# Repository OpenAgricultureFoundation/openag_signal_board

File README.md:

# openag_signal_board
Shield for Arduino Mega to easily connect sensors and other communication devices.

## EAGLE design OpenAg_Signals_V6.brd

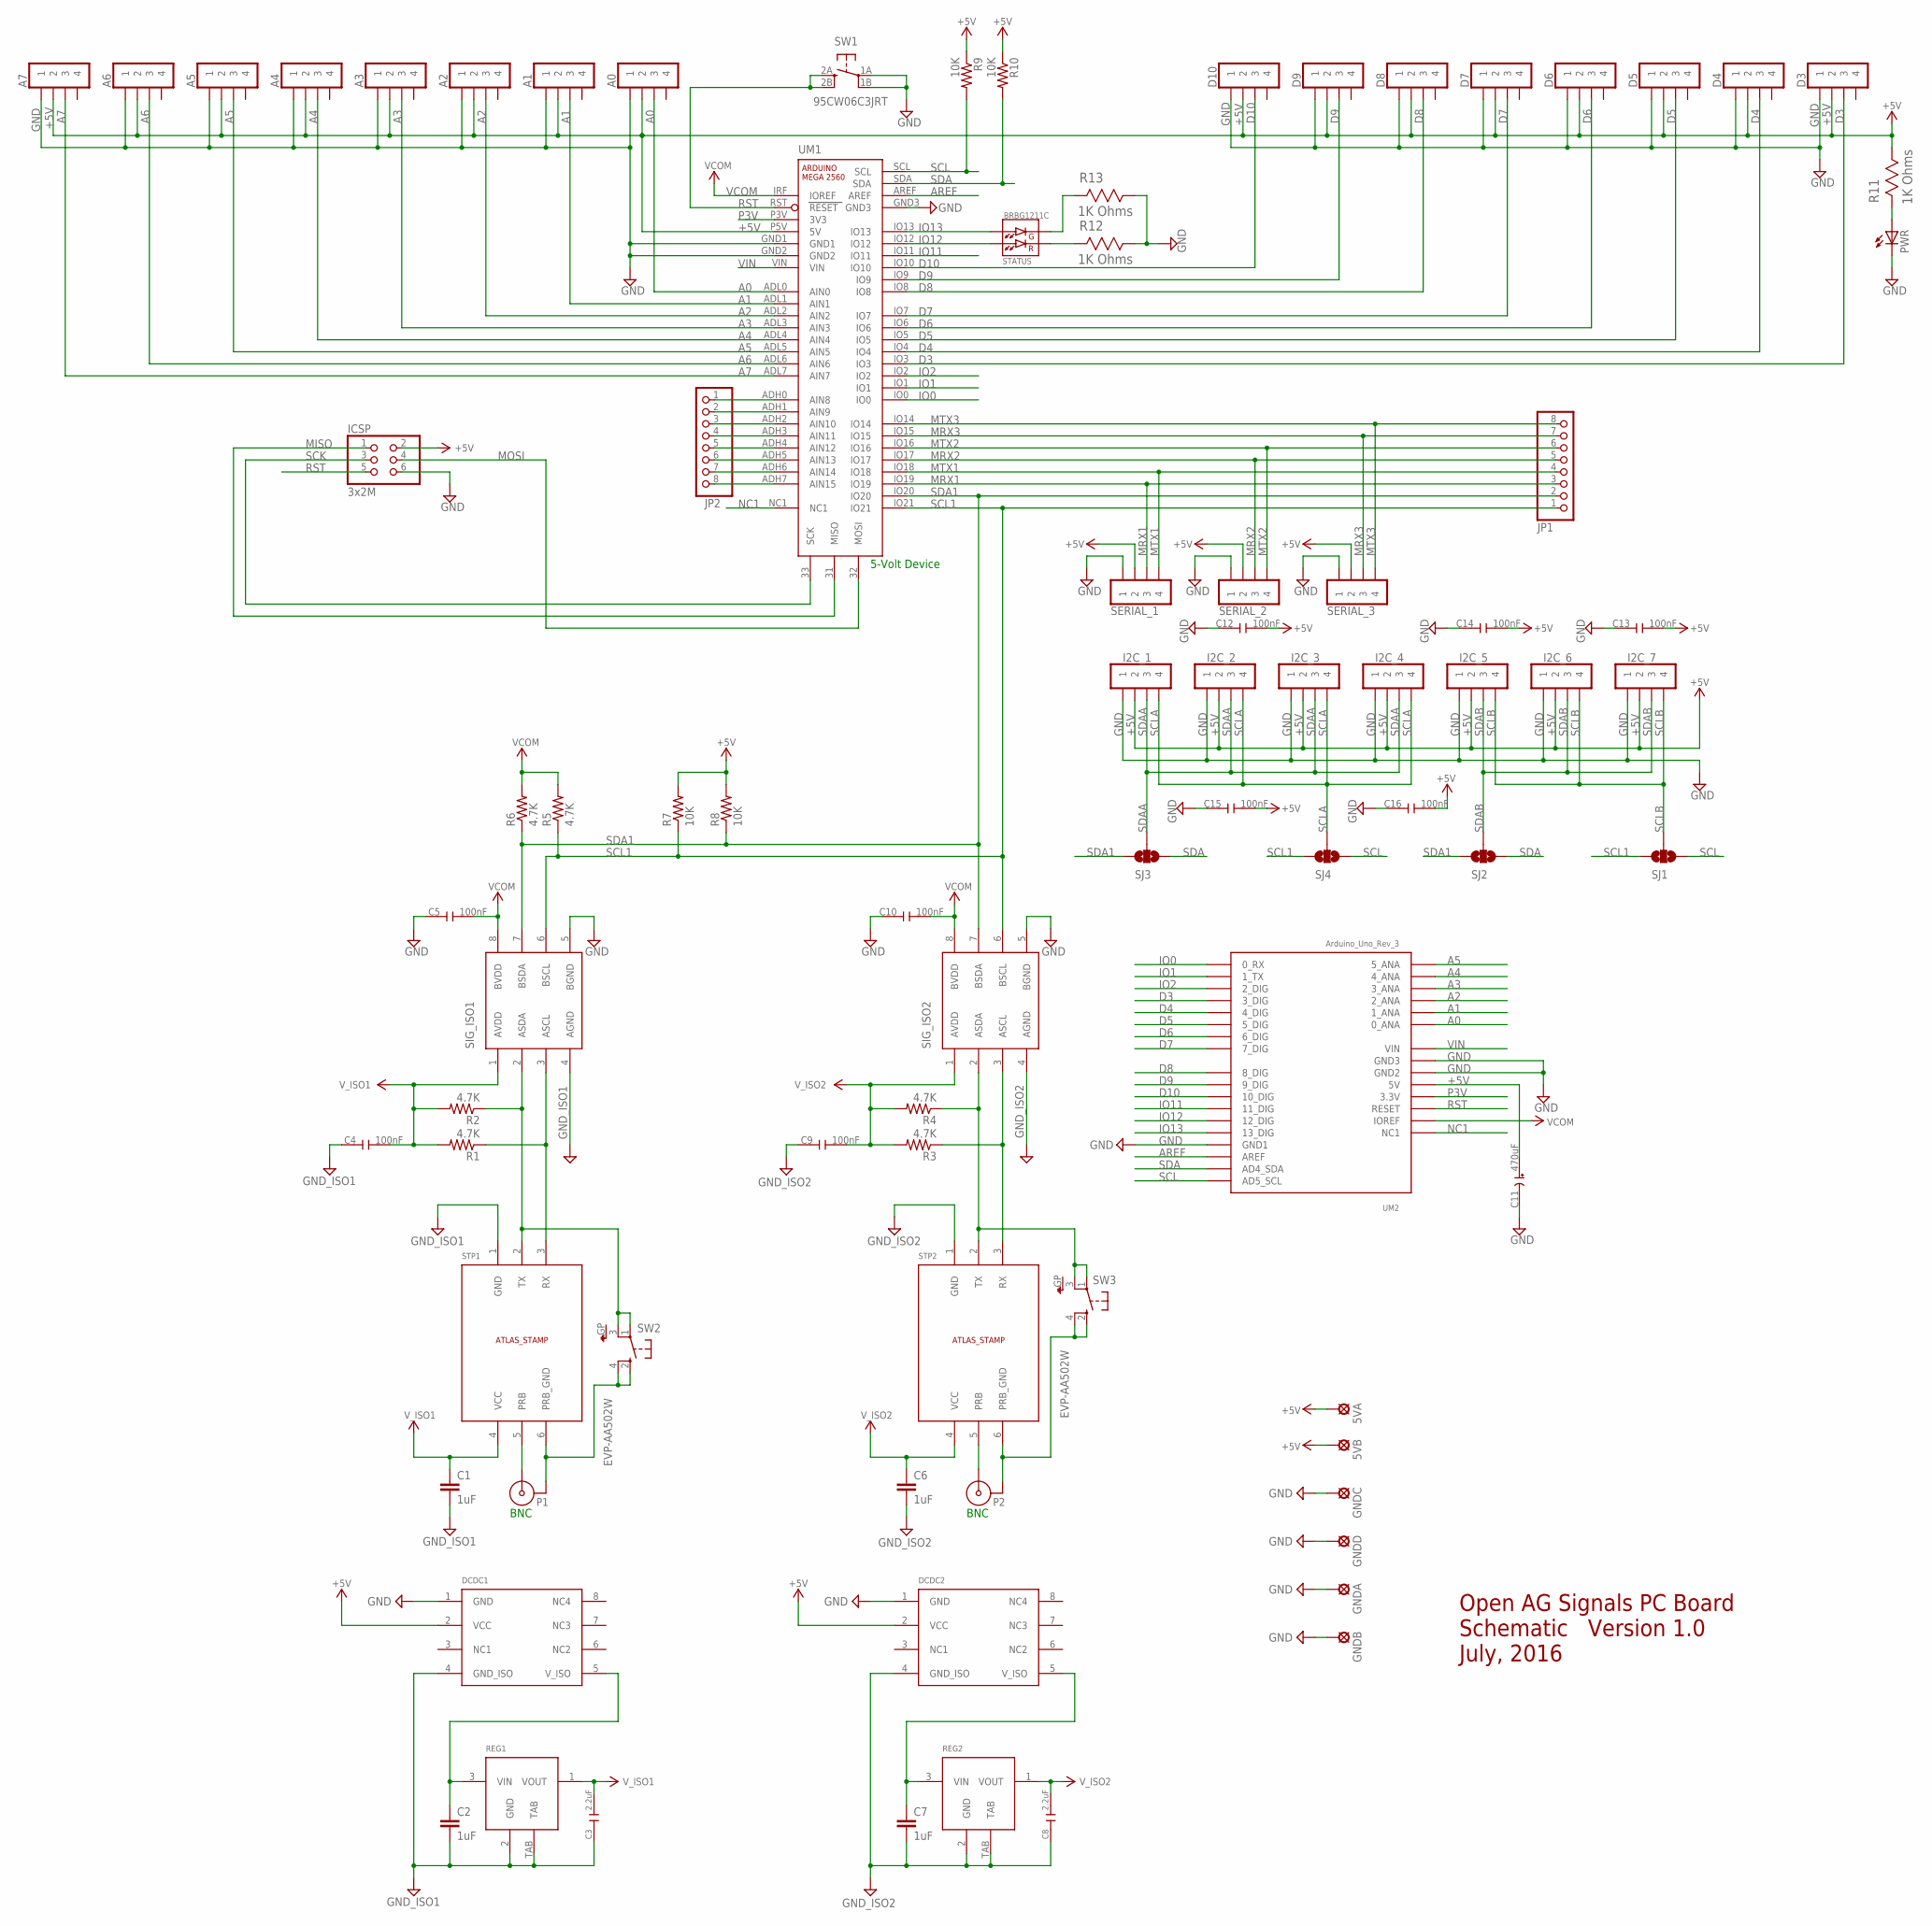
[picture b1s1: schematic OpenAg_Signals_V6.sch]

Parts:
5VA, 5VB: PAD070
A0, A1, A2, A3, A4, A5, A6, A7: MOLEX_0705430003
C1, C2, C6, C7: 1uF; 0805
C3, C8: 2.2uF; M0805
C4, C5, C9, C10, C12, C13, C14, C15, C16: C-N-100.0N-X7R-25V-10P-0805; M0805
C11: T495X477K010ATE100; M2917
D3, D4, D5, D6, D7, D8, D9, D10: MOLEX_0705430003
DCDC1, DCDC2: RECOM_R1SE_0505_R
GNDA: PAD070
GNDB: PAD070
GNDC: PAD070
GNDD: PAD070
I2C_1, I2C_2, I2C_3, I2C_4, I2C_5, I2C_6, I2C_7: MOLEX_0705430003
ICSP: 3x2M; 2X03
JP1, JP2: PINHD-1X8BIG; 1X08-BIG
P1, P2: BNC_TE_1_1337542_0; BNC_FEMALE_PANEL_RGT_ANGLE_MNT
PWR: LED_LEDCHIPLED_0805; LED_CHIPLED_0805
R1, R2, R3, R4, R5, R6: 4.7K; 0805
R7, R8, R9, R10: 10K; 0603-RES
R11, R12, R13: 1K Ohms; RESC1608X60N
REG1, REG2: LD2981ABU50TR; SOT89
SERIAL_1, SERIAL_2, SERIAL_3: MOLEX_0705430003
SIG_ISO1, SIG_ISO2: SI8600AC-B-IS; SO8ISO
SJ1, SJ2, SJ3, SJ4: SOLDERJUMPER_2WAYT; SJ_2
STATUS: LED-REDGRN-BRBG1211C; BILED-0605
STP1, STP2: ATLAS_SCIENTIFIC_STAMP
SW1: 95CW06C3JRT; GRAYHILL_95CW06C3JRT
SW2, SW3: EVP-AA502W; PANASONIC-EVP-AA502W
UM1: ARDUINO_MEGA_2560_R3_SIDES; ARDUINO_MEGA_2560_R3_CONNECTORS
UM2: ARDUINO_UNO_REV3_SOCKET

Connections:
+5V: 5VA.1, 5VB.1, A0.2, A1.2, A2.2, A3.2, A4.2, A5.2, A6.2, A7.2, C11.P, C12.2, C13.2, C14.2, C15.2, C16.2, D3.2, D4.2, D5.2, D6.2, D7.2, D8.2, D9.2, D10.2, DCDC1.2 (VCC), DCDC2.2 (VCC), I2C_1.2, I2C_2.2, I2C_3.2, I2C_4.2, I2C_5.2, I2C_6.2, I2C_7.2, ICSP.2, R7.2, R8.2, R9.1, R10.1, R11.1, SERIAL_1.2, SERIAL_2.2, SERIAL_3.2, UM1.P5V (5V), UM2.PWR_5V (5V)
A0: A0.3, UM1.ADL0 (AIN0), UM2.AD0 (0_ANA)
A1: A1.3, UM1.ADL1 (AIN1), UM2.AD1 (1_ANA)
A2: A2.3, UM1.ADL2 (AIN2), UM2.AD2 (2_ANA)
A3: A3.3, UM1.ADL3 (AIN3), UM2.AD3 (3_ANA)
A4: A4.3, UM1.ADL4 (AIN4), UM2.AD4 (4_ANA)
A5: A5.3, UM1.ADL5 (AIN5), UM2.AD5 (5_ANA)
A6: A6.3, UM1.ADL6 (AIN6)
A7: A7.3, UM1.ADL7 (AIN7)
AREF: UM1.AREF, UM2.IOH15 (AREF)
D3: D3.3, UM1.IO3, UM2.IOL3 (3_DIG)
D4: D4.3, UM1.IO4, UM2.IOL4 (4_DIG)
D5: D5.3, UM1.IO5, UM2.IOL5 (5_DIG)
D6: D6.3, UM1.IO6, UM2.IOL6 (6_DIG)
D7: D7.3, UM1.IO7, UM2.IOL7 (7_DIG)
D8: D8.3, UM1.IO8, UM2.IOH8 (8_DIG)
D9: D9.3, UM1.IO9, UM2.IOH9 (9_DIG)
D10: D10.3, UM1.IO10, UM2.IOH10 (10_DIG)
GND: A0.1, A1.1, A2.1, A3.1, A4.1, A5.1, A6.1, A7.1, C5.1, C10.1, C11.N, C12.1, C13.1, C14.1, C15.1, C16.1, D3.1, D4.1, D5.1, D6.1, D7.1, D8.1, D9.1, D10.1, DCDC1.1 (GND), DCDC2.1 (GND), GNDA.1, GNDB.1, GNDC.1, GNDD.1, I2C_1.1, I2C_2.1, I2C_3.1, I2C_4.1, I2C_5.1, I2C_6.1, I2C_7.1, ICSP.6, PWR.C, R12.1, R13.1, SERIAL_1.1, SERIAL_2.1, SERIAL_3.1, SIG_ISO1.5 (BGND), SIG_ISO2.5 (BGND), SW1.1A (PA1), SW1.1B (PA2), UM1.GND1, UM1.GND2, UM1.GND3, UM2.IOH14 (GND1), UM2.PWR_GND2 (GND2), UM2.PWR_GND3 (GND3)
GND_ISO1: C1.2, C2.2, C3.1, C4.1, DCDC1.4 (GND_ISO), REG1.2 (GND), REG1.TAB, SIG_ISO1.4 (AGND), STP1.1 (GND)
GND_ISO2: C6.2, C7.2, C8.1, C9.1, DCDC2.4 (GND_ISO), REG2.2 (GND), REG2.TAB, SIG_ISO2.4 (AGND), STP2.1 (GND)
IO0: UM1.IO0, UM2.IOL0 (0_RX)
IO1: UM1.IO1, UM2.IOL1 (1_TX)
IO2: UM1.IO2, UM2.IOL2 (2_DIG)
IO11: UM1.IO11, UM2.IOH11 (11_DIG)
IO12: STATUS.1 (RA), UM1.IO12, UM2.IOH12 (12_DIG)
IO13: STATUS.3 (GA), UM1.IO13, UM2.IOH13 (13_DIG)
MISO: ICSP.1, UM1.31 (MISO)
MOSI: ICSP.4, UM1.32 (MOSI)
MRX1: JP1.3, SERIAL_1.3, UM1.IO19
MRX2: JP1.5, SERIAL_2.3, UM1.IO17
MRX3: JP1.7, SERIAL_3.3, UM1.IO15
MTX1: JP1.4, SERIAL_1.4, UM1.IO18
MTX2: JP1.6, SERIAL_2.4, UM1.IO16
MTX3: JP1.8, SERIAL_3.4, UM1.IO14
unnamed: P1.1, STP1.5 (PRB)
unnamed: R12.2, STATUS.2 (RC)
unnamed: PWR.A, R11.2
unnamed: R1.1, SIG_ISO1.3 (ASCL), STP1.3 (RX)
unnamed: R2.1, SIG_ISO1.2 (ASDA), STP1.2 (TX), SW2.1, SW2.3
unnamed: P1.2 (G1), STP1.6 (PRB_GND), SW2.2, SW2.4
unnamed: P2.1, STP2.5 (PRB)
unnamed: R13.2, STATUS.4 (GC)
unnamed: R3.1, SIG_ISO2.3 (ASCL), STP2.3 (RX)
unnamed: P2.2 (G1), STP2.6 (PRB_GND), SW3.2, SW3.4
unnamed: C2.1, DCDC1.5 (V_ISO), REG1.3 (VIN)
unnamed: C7.1, DCDC2.5 (V_ISO), REG2.3 (VIN)
unnamed: R4.1, SIG_ISO2.2 (ASDA), STP2.2 (TX), SW3.1, SW3.3
unnamed: JP2.8, UM1.ADH7 (AIN15)
unnamed: JP2.7, UM1.ADH6 (AIN14)
unnamed: JP2.6, UM1.ADH5 (AIN13)
unnamed: JP2.5, UM1.ADH4 (AIN12)
unnamed: JP2.4, UM1.ADH3 (AIN11)
unnamed: JP2.3, UM1.ADH2 (AIN10)
unnamed: JP2.2, UM1.ADH1 (AIN9)
unnamed: JP2.1, UM1.ADH0 (AIN8)
NC1: UM1.NC1, UM2.PWR_NC (NC1)
P3V: UM1.P3V (3V3), UM2.PWR_3_3V (3.3V)
RST: ICSP.5, SW1.2A (PB1), SW1.2B (PB2), UM1.RST (RESET), UM2.PWR_RESET (RESET)
SCK: ICSP.3, UM1.33 (SCK)
SCL: R9.2, SJ1.1, SJ4.1, UM1.SCL, UM2.IOH17 (AD5_SCL)
SCL1: JP1.1, R5.1, R7.1, SIG_ISO1.6 (BSCL), SIG_ISO2.6 (BSCL), SJ1.3, SJ4.3, UM1.IO21
SCLA: I2C_1.4, I2C_2.4, I2C_3.4, I2C_4.4, SJ4.2
SCLB: I2C_5.4, I2C_6.4, I2C_7.4, SJ1.2
SDA: R10.2, SJ2.1, SJ3.1, UM1.SDA, UM2.IOH16 (AD4_SDA)
SDA1: JP1.2, R6.1, R8.1, SIG_ISO1.7 (BSDA), SIG_ISO2.7 (BSDA), SJ2.3, SJ3.3, UM1.IO20
SDAA: I2C_1.3, I2C_2.3, I2C_3.3, I2C_4.3, SJ3.2
SDAB: I2C_5.3, I2C_6.3, I2C_7.3, SJ2.2
VCOM: C5.2, C10.2, R5.2, R6.2, SIG_ISO1.8 (BVDD), SIG_ISO2.8 (BVDD), UM1.IRF (IOREF), UM2.PWR_IOREF (IOREF)
VIN: UM1.VIN, UM2.PWR_VIN (VIN)
V_ISO1: C1.1, C3.2, C4.2, R1.2, R2.2, REG1.1 (VOUT), SIG_ISO1.1 (AVDD), STP1.4 (VCC)
V_ISO2: C6.1, C8.2, C9.2, R3.2, R4.2, REG2.1 (VOUT), SIG_ISO2.1 (AVDD), STP2.4 (VCC)

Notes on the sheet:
BNC
5-Volt Device
Open AG Signals PC Board Schematic Version 1.0 July, 2016

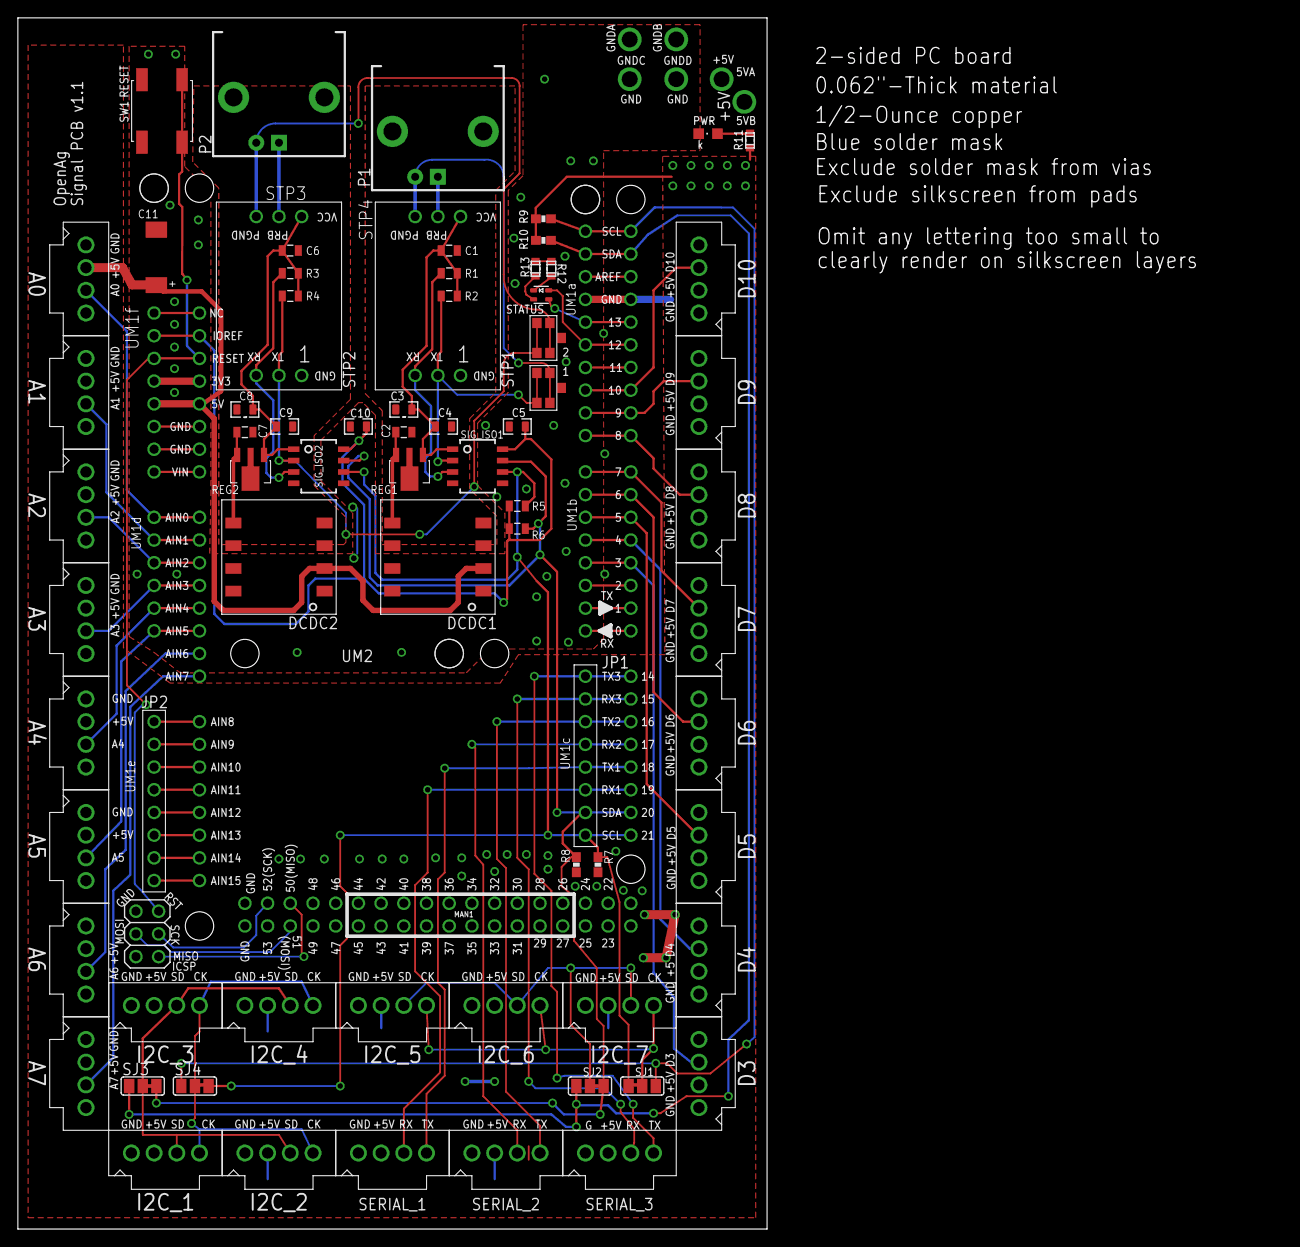
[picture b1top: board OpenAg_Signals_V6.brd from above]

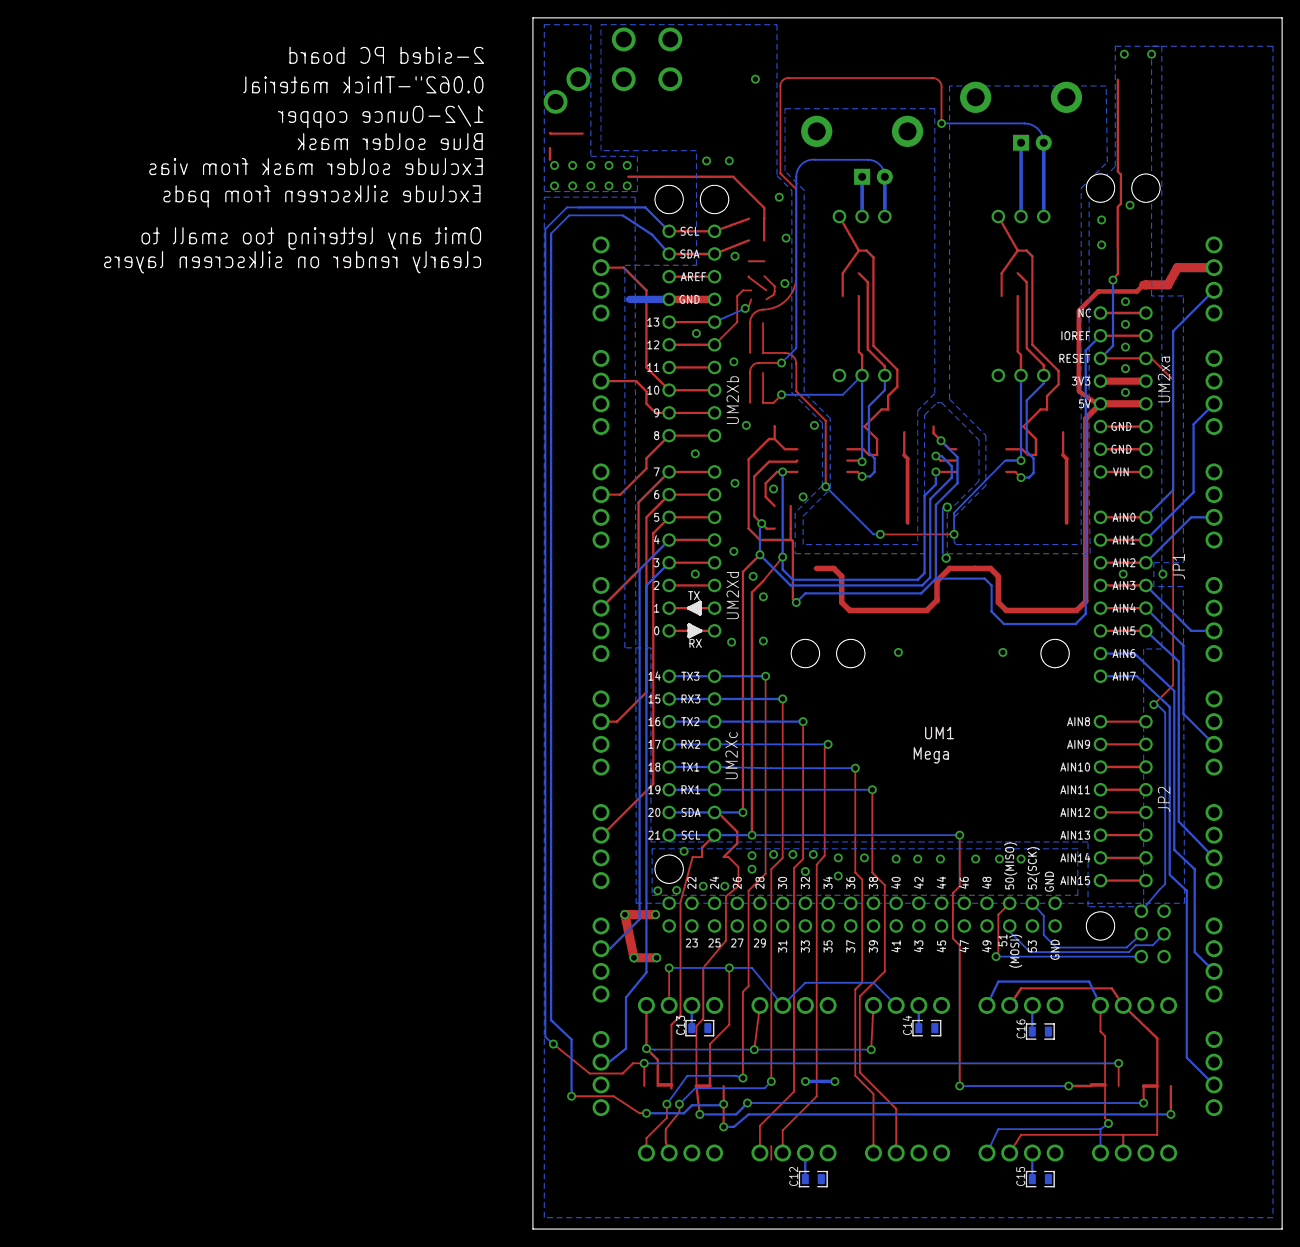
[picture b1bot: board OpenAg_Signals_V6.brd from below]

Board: 2 copper layers, 141.4 x 135.5 mm, 85 parts (5 on the bottom side), 72 nets.

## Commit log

2017-01-09 Added .brd, .sch and gerber files
2017-06-13 Added cleaned up BOM in .xyrs from francoisnyc for use with MACROFAB

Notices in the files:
parts and their libraries:
SparkFun: Licensing: CC v3.0 Share-Alike You are welcome to use this library for commercial purposes.
SparkFun-Capacitors: Licensing: Creative Commons ShareAlike 4.0 International - https://creativecommons.org/licenses/by-sa/4.0
